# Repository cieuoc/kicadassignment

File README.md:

## Assignment

Each directory contains a specific KiCAD assignment problem.

+ Login to your github account
+ Fork this repository
+ Make a local copy using 'git clone <repo link address>'
+ View the README file inside the directory with your name
+ Create a KiCAD project inside the directory with your name
  + Create schematic diagram
  + Create any new symbols if needed
  + Take a screenshot of the schematic and place it in this directory
  + Git add all files
  + Git commit
  + Associate footprints
  + Create Layout
  + Take a screenshot of the layout and place it in this directory
  + Git add all files
  + Git commit
+ git push origin main
+ create a pull request

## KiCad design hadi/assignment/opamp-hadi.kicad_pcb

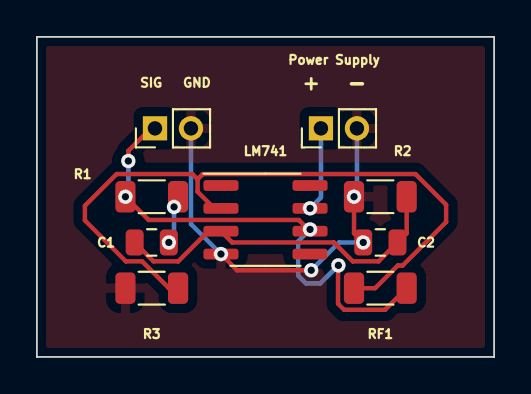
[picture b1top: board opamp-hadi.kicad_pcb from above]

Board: 2 copper layers, 25.4 x 17.8 mm, 9 parts (0 on the bottom side), 6 nets.

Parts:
C1, C2: 1nF; C_0805_2012Metric
J1: +; PinHeader_1x02_P2.00mm_Vertical
J2: SIG; PinHeader_1x02_P2.00mm_Vertical
R1, R2: 3.18k; R_1206_3216Metric
R3: 1k; R_1206_3216Metric
RF1: 2.2k; R_1206_3216Metric
U1: LM741; SOIC-8_3.9x4.9mm_P1.27mm

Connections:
GND: C2.2, J1.2, J2.2, R2.2, R3.2, U1.4 (V-)
unnamed: C1.1, R1.1
unnamed: C1.2, C2.1, R2.1, U1.3 (+)
unnamed: J2.1, R1.2, RF1.1, U1.6
unnamed: R3.1, RF1.2, U1.2 (-)
unnamed: J1.1, U1.7 (V+)

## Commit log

2024-11-04 added assignments
2024-11-04 added files
2024-11-04 old_data
2024-11-06 Added Pics of schematic, pcb and 3d layout
2024-11-06 Added Gerber files
2024-11-06 Added Gerber.zip file
2024-11-06 babu
2024-11-06 sinewave_gen
2024-11-06 sinewave
2024-11-06 voltage rerulator
2024-11-06 Added pics of corrected version
2024-11-06 Updated version of assignment
2024-11-11 half_adder
2024-11-11 Added zip file of project
2024-11-13 add assingment
2024-11-13 assigment
    voltage follower by rinu rishana
2024-11-18 555 BLINKER CIRCUIT ASSIGNMENT UPLOADED
2024-11-20 new assignment
